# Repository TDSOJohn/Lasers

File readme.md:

# Monochrome Laser Bar

This repo contains the schematics and software for the monochrome laser bars used by VirtualConcrete.

Hardware:
- Aluminum body
- Up to 6 laser diodes
- Custom designed pcb with [Arduino Nano](https://docs.arduino.cc/hardware/nano/) and up to 6 laser drivers
- Custom variation of ethernet poe to supply everything with a single RJ45
- DMX over RJ45 control mode
- Fun mode

Software:
- Reads DMX input using [DMXSerial](https://github.com/mathertel/DMXSerial)
- Writes dimmer values as PWM

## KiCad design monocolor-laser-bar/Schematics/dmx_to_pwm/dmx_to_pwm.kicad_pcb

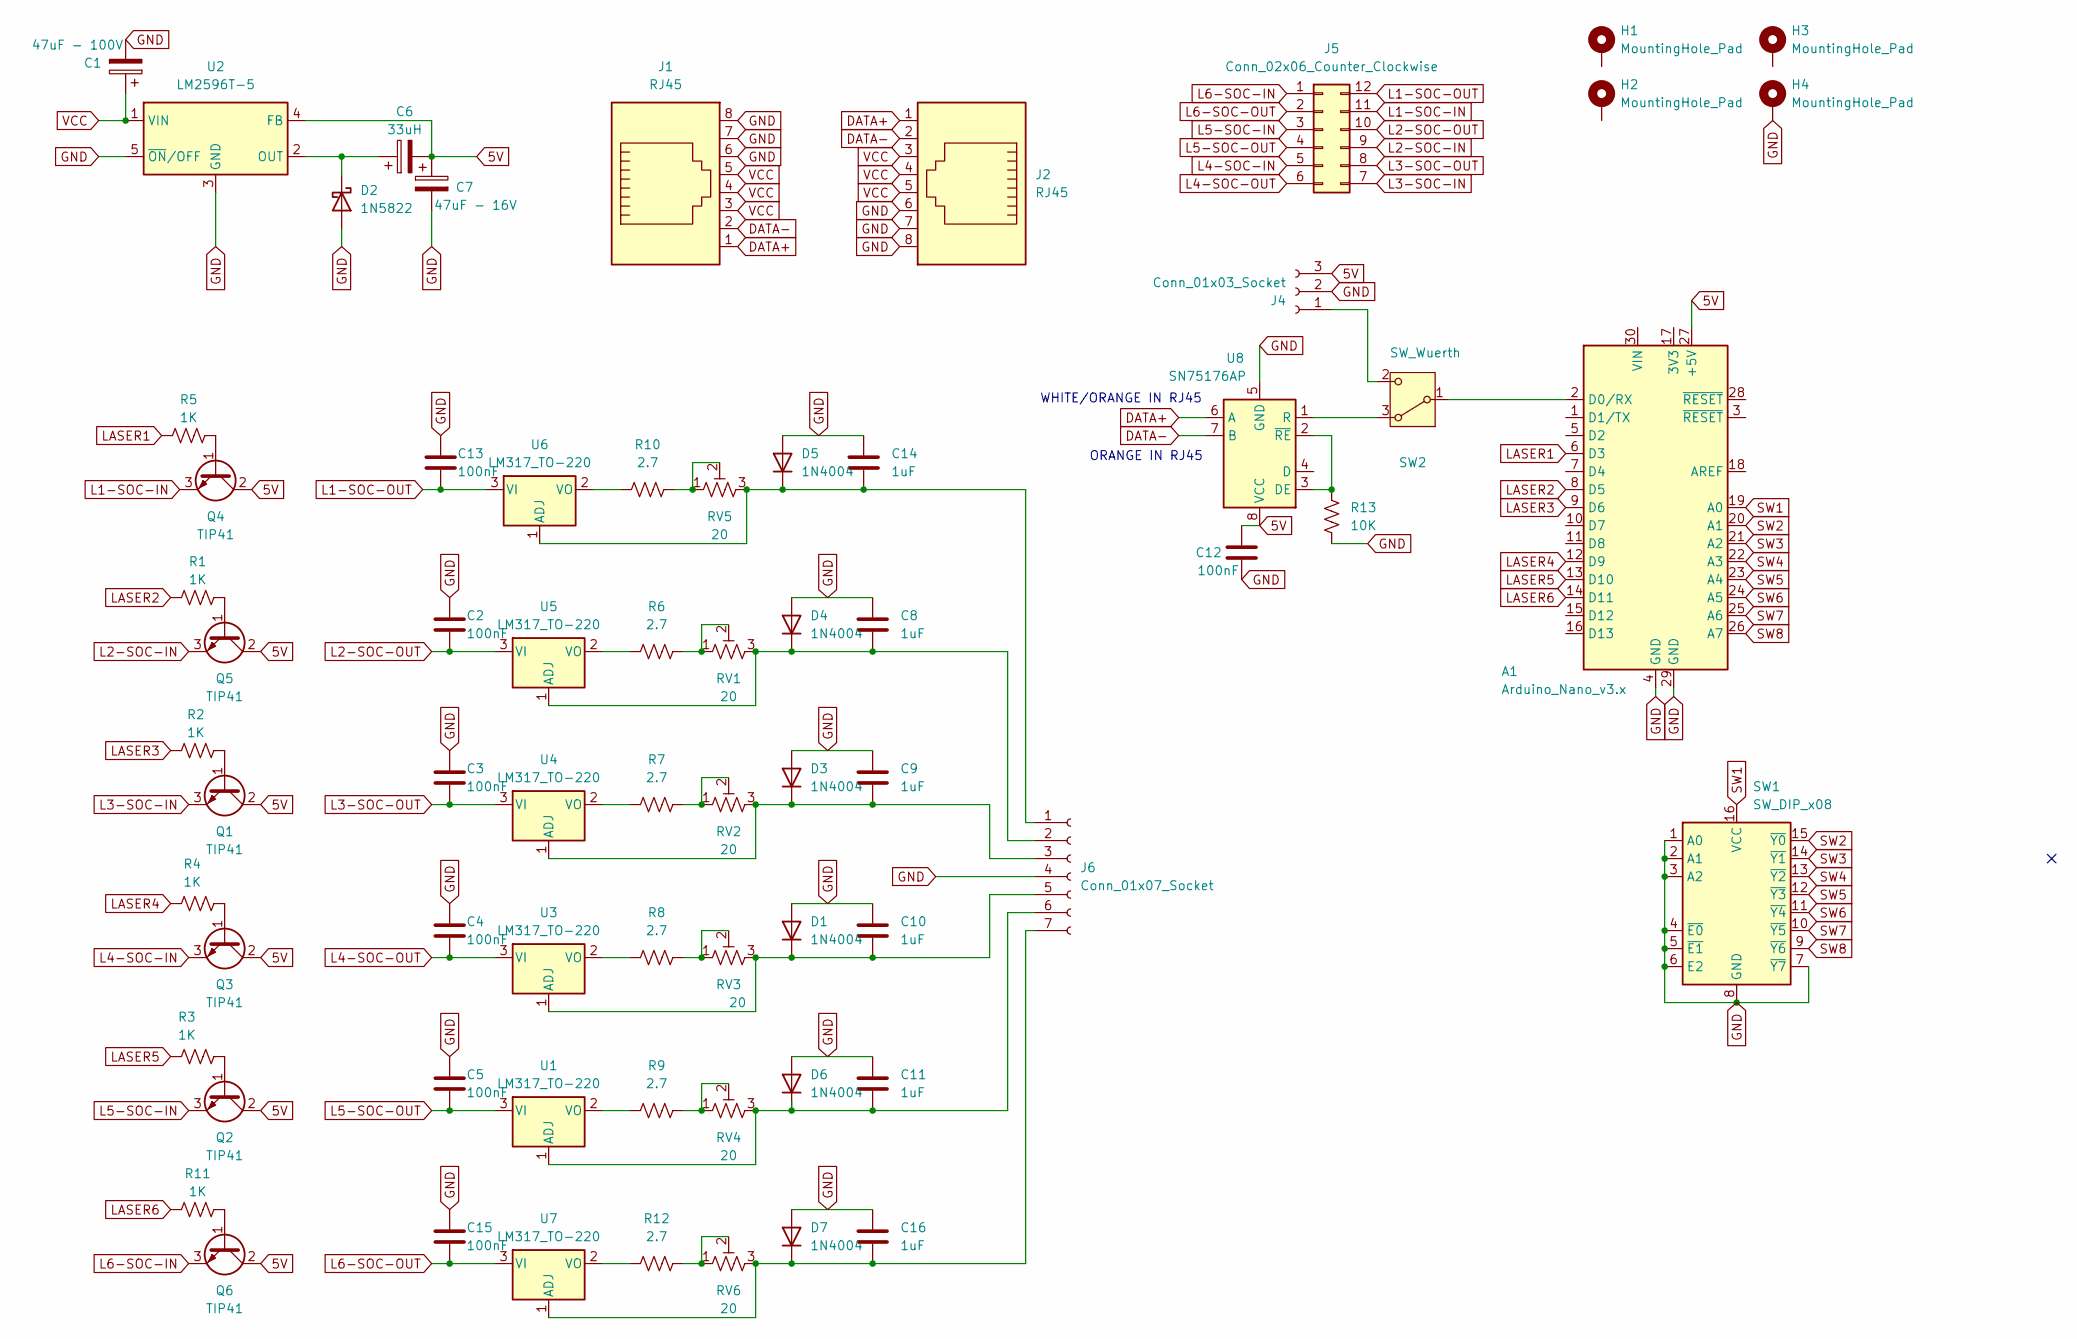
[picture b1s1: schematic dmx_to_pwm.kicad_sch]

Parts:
A1: Arduino_Nano_v3.x; Arduino_Nano
C1: 47uF - 100V; CP_Radial_D7.5mm_P2.50mm
C2, C3, C4, C5, C12, C13, C15: 100nF; C_Disc_D3.0mm_W2.0mm_P2.50mm
C6: 33uH; CP_Radial_D8.0mm_P5.00mm
C7: 47uF - 16V; CP_Radial_D7.5mm_P2.50mm
C8, C9, C10, C11, C14, C16: 1uF; C_Disc_D3.0mm_W2.0mm_P2.50mm
D1, D3, D4, D5, D6, D7: 1N4004; D_DO-41_SOD81_P7.62mm_Horizontal
D2: 1N5822; D_DO-201AD_P15.24mm_Horizontal
H1, H2, H3, H4: MountingHole_Pad; MountingHole_3.2mm_M3_Pad
J1, J2: RJ45; RJ45_Amphenol_54602-x08_Horizontal
J4: Conn_01x03_Socket; JST_EH_B3B-EH-A_1x03_P2.50mm_Vertical
J5: Conn_02x06_Counter_Clockwise; PinHeader_2x06_P2.54mm_Vertical
J6: Conn_01x07_Socket; JST_EH_B7B-EH-A_1x07_P2.50mm_Vertical
Q1, Q2, Q3, Q4, Q5, Q6: TIP41; TO-220-3_Vertical
R1, R2, R3, R4, R5, R11: 1K; R_Axial_DIN0207_L6.3mm_D2.5mm_P7.62mm_Horizontal
R6, R7, R8, R9, R10, R12: 2.7; R_Axial_DIN0411_L9.9mm_D3.6mm_P12.70mm_Horizontal
R13: 10K; R_Axial_DIN0414_L11.9mm_D4.5mm_P7.62mm_Vertical
RV1, RV2, RV3, RV4, RV5, RV6: 20; Potentiometer_Bourns_3296Z_Horizontal
SW1: SW_DIP_x08; DIP-16_W7.62mm_LongPads
SW2: SW_Wuerth; SW_Slide-03_Wuerth-WS-SLTV_10x2.5x6.4_P2.54mm
U1, U3, U4, U5, U6, U7: LM317_TO-220; TO-220-3_Vertical
U2: LM2596T-5; TO-220-5_P3.4x3.7mm_StaggerOdd_Lead3.8mm_Vertical
U8: SN75176AP; DIP-8_W7.62mm_Socket_LongPads

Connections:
5V: A1.27 (+5V), C6.2, C7.1, C12.1, J4.3, Q1.2 (C), Q2.2 (C), Q3.2 (C), Q4.2 (C), Q5.2 (C), Q6.2 (C), U2.4 (FB), U8.8 (VCC)
DATA+: J1.1, J2.1, U8.6 (A)
DATA-: J1.2, J2.2, U8.7 (B)
GND: A1.4 (GND), A1.29 (GND), C1.2, C2.1, C3.1, C4.1, C5.1, C7.2, C8.1, C9.1, C10.1, C11.1, C12.2, C13.1, C14.1, C15.1, C16.1, D1.2 (A), D2.2 (A), D3.2 (A), D4.2 (A), D5.2 (A), D6.2 (A), D7.2 (A), H4.1, J1.6, J1.7, J1.8, J2.6, J2.7, J2.8, J4.2, J6.4, R13.1, SW1.1 (A0), SW1.2 (A1), SW1.3 (A2), SW1.4 (~E0), SW1.5 (~E1), SW1.6 (E2), SW1.7 (~Y7), SW1.8 (GND), U2.3 (GND), U2.5 (~ON/OFF), U8.5 (GND)
L1-SOC-IN: J5.11, Q4.3 (E)
L1-SOC-OUT: C13.2, J5.12, U6.3 (VI)
L2-SOC-IN: J5.9, Q5.3 (E)
L2-SOC-OUT: C2.2, J5.10, U5.3 (VI)
L3-SOC-IN: J5.7, Q1.3 (E)
L3-SOC-OUT: C3.2, J5.8, U4.3 (VI)
L4-SOC-IN: J5.5, Q3.3 (E)
L4-SOC-OUT: C4.2, J5.6, U3.3 (VI)
L5-SOC-IN: J5.3, Q2.3 (E)
L5-SOC-OUT: C5.2, J5.4, U1.3 (VI)
L6-SOC-IN: J5.1, Q6.3 (E)
L6-SOC-OUT: C15.2, J5.2, U7.3 (VI)
LASER1: A1.6 (D3), R5.2
LASER2: A1.8 (D5), R1.2
LASER3: A1.9 (D6), R2.2
LASER4: A1.12 (D9), R4.2
LASER5: A1.13 (D10), R3.2
LASER6: A1.14 (D11), R11.2
unnamed: A1.2 (D0/RX), SW2.1 (B)
unnamed: C10.2, D1.1 (K), J6.5, RV3.3, U3.1 (ADJ)
unnamed: C6.1, D2.1 (K), U2.2 (OUT)
unnamed: C9.2, D3.1 (K), J6.3, RV2.3, U4.1 (ADJ)
unnamed: C8.2, D4.1 (K), J6.2, RV1.3, U5.1 (ADJ)
unnamed: C14.2, D5.1 (K), J6.1, RV5.3, U6.1 (ADJ)
unnamed: C11.2, D6.1 (K), J6.6, RV4.3, U1.1 (ADJ)
unnamed: C16.2, D7.1 (K), J6.7, RV6.3, U7.1 (ADJ)
unnamed: J4.1, SW2.2 (C)
unnamed: Q1.1 (B), R2.1
unnamed: Q2.1 (B), R3.1
unnamed: Q3.1 (B), R4.1
unnamed: Q4.1 (B), R5.1
unnamed: Q5.1 (B), R1.1
unnamed: Q6.1 (B), R11.1
unnamed: R6.1, RV1.1, RV1.2
unnamed: R7.1, RV2.1, RV2.2
unnamed: R8.1, RV3.1, RV3.2
unnamed: R9.1, RV4.1, RV4.2
unnamed: R10.1, RV5.1, RV5.2
unnamed: R12.1, RV6.1, RV6.2
unnamed: SW2.3 (A), U8.1 (R)
unnamed: R9.2, U1.2 (VO)
unnamed: R8.2, U3.2 (VO)
unnamed: R7.2, U4.2 (VO)
unnamed: R6.2, U5.2 (VO)
unnamed: R10.2, U6.2 (VO)
unnamed: R12.2, U7.2 (VO)
unnamed: R13.2, U8.2 (~RE), U8.3 (DE)
SW1: A1.19 (A0), SW1.16 (VCC)
SW2: A1.20 (A1), SW1.15 (~Y0)
SW3: A1.21 (A2), SW1.14 (~Y1)
SW4: A1.22 (A3), SW1.13 (~Y2)
SW5: A1.23 (A4), SW1.12 (~Y3)
SW6: A1.24 (A5), SW1.11 (~Y4)
SW7: A1.25 (A6), SW1.10 (~Y5)
SW8: A1.26 (A7), SW1.9 (~Y6)
VCC: C1.1, J1.3, J1.4, J1.5, J2.3, J2.4, J2.5, U2.1 (VIN)

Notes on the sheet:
WHITE/ORANGE IN RJ45
ORANGE IN RJ45

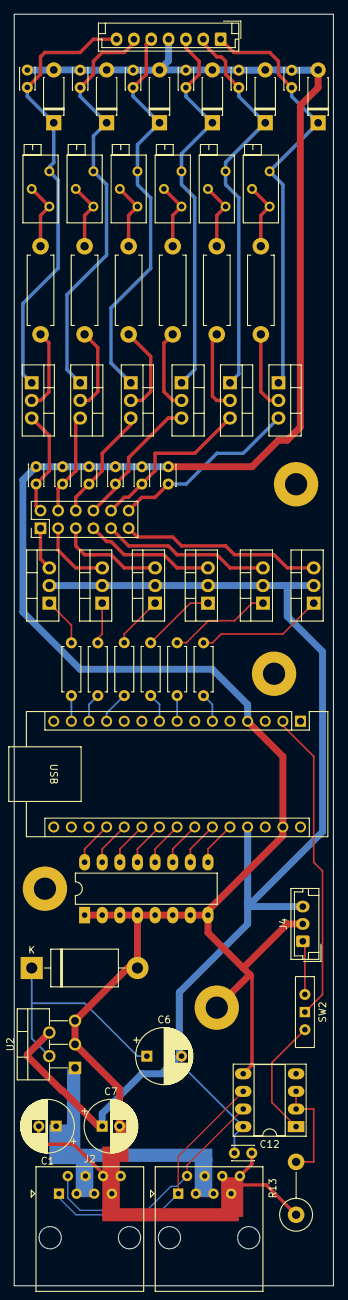
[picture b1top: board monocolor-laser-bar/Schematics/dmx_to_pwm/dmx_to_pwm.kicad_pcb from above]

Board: 2 copper layers, 46.0 x 183.2 mm, 68 parts (0 on the bottom side), 60 nets.

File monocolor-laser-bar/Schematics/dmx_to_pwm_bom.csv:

"Id";"Designator";"Footprint";"Quantity";"Designation";"Supplier and ref";
1;"C10,C14,C9,C16,C8,C11";"C_Disc_D3.0mm_W2.0mm_P2.50mm";6;"1uF";;;
2;"C5,C4,C2,C12,C13,C3,C15";"C_Disc_D3.0mm_W2.0mm_P2.50mm";7;"100nF";;;
3;"D7,D6,D1,D5,D3,D4";"D_DO-41_SOD81_P7.62mm_Horizontal";6;"1N4004";;;
4;"C6";"CP_Radial_D8.0mm_P5.00mm";1;"33uH";;;
5;"U7,U3,U4,U5,U1,U6";"TO-220-3_Vertical";6;"LM317_TO-220";;;
6;"RV2,RV3,RV4,RV6,RV1,RV5";"Potentiometer_Bourns_3296Z_Horizontal";6;"20";;;
7;"C7";"CP_Radial_D7.5mm_P2.50mm";1;"47uF - 16V";;;
8;"D2";"D_DO-201AD_P15.24mm_Horizontal";1;"1N5822";;;
9;"R5,R4,R2,R3,R1,R11";"R_Axial_DIN0207_L6.3mm_D2.5mm_P7.62mm_Horizontal";6;"1K";;;
10;"R9,R6,R8,R7,R12,R10";"R_Axial_DIN0411_L9.9mm_D3.6mm_P12.70mm_Horizontal";6;"2.7";;;
11;"Q6,Q5,Q2,Q3,Q1,Q4";"TO-220-3_Vertical";6;"TIP41";;;
12;"J5";"PinHeader_2x06_P2.54mm_Vertical";1;"Conn_02x06_Counter_Clockwise";;;
13;"R13";"R_Axial_DIN0414_L11.9mm_D4.5mm_P7.62mm_Vertical";1;"10K";;;
14;"J1,J2";"RJ45_Amphenol_54602-x08_Horizontal";2;"RJ45";;;
15;"SW1";"DIP-16_W7.62mm_LongPads";1;"SW_DIP_x08";;;
16;"J4";"JST_EH_B3B-EH-A_1x03_P2.50mm_Vertical";1;"Conn_01x03_Socket";;;
17;"U2";"TO-220-5_P3.4x3.7mm_StaggerOdd_Lead3.8mm_Vertical";1;"LM2596T-5";;;
18;"U8";"DIP-8_W7.62mm_Socket_LongPads";1;"SN75176AP";;;
19;"C1";"CP_Radial_D7.5mm_P2.50mm";1;"47uF - 100V";;;
20;"SW2";"SW_Slide-03_Wuerth-WS-SLTV_10x2.5x6.4_P2.54mm";1;"SW_Wuerth";;;
21;"J6";"JST_EH_B7B-EH-A_1x07_P2.50mm_Vertical";1;"Conn_01x07_Socket";;;
22;"A1";"Arduino_Nano";1;"Arduino_Nano_v3.x";;;

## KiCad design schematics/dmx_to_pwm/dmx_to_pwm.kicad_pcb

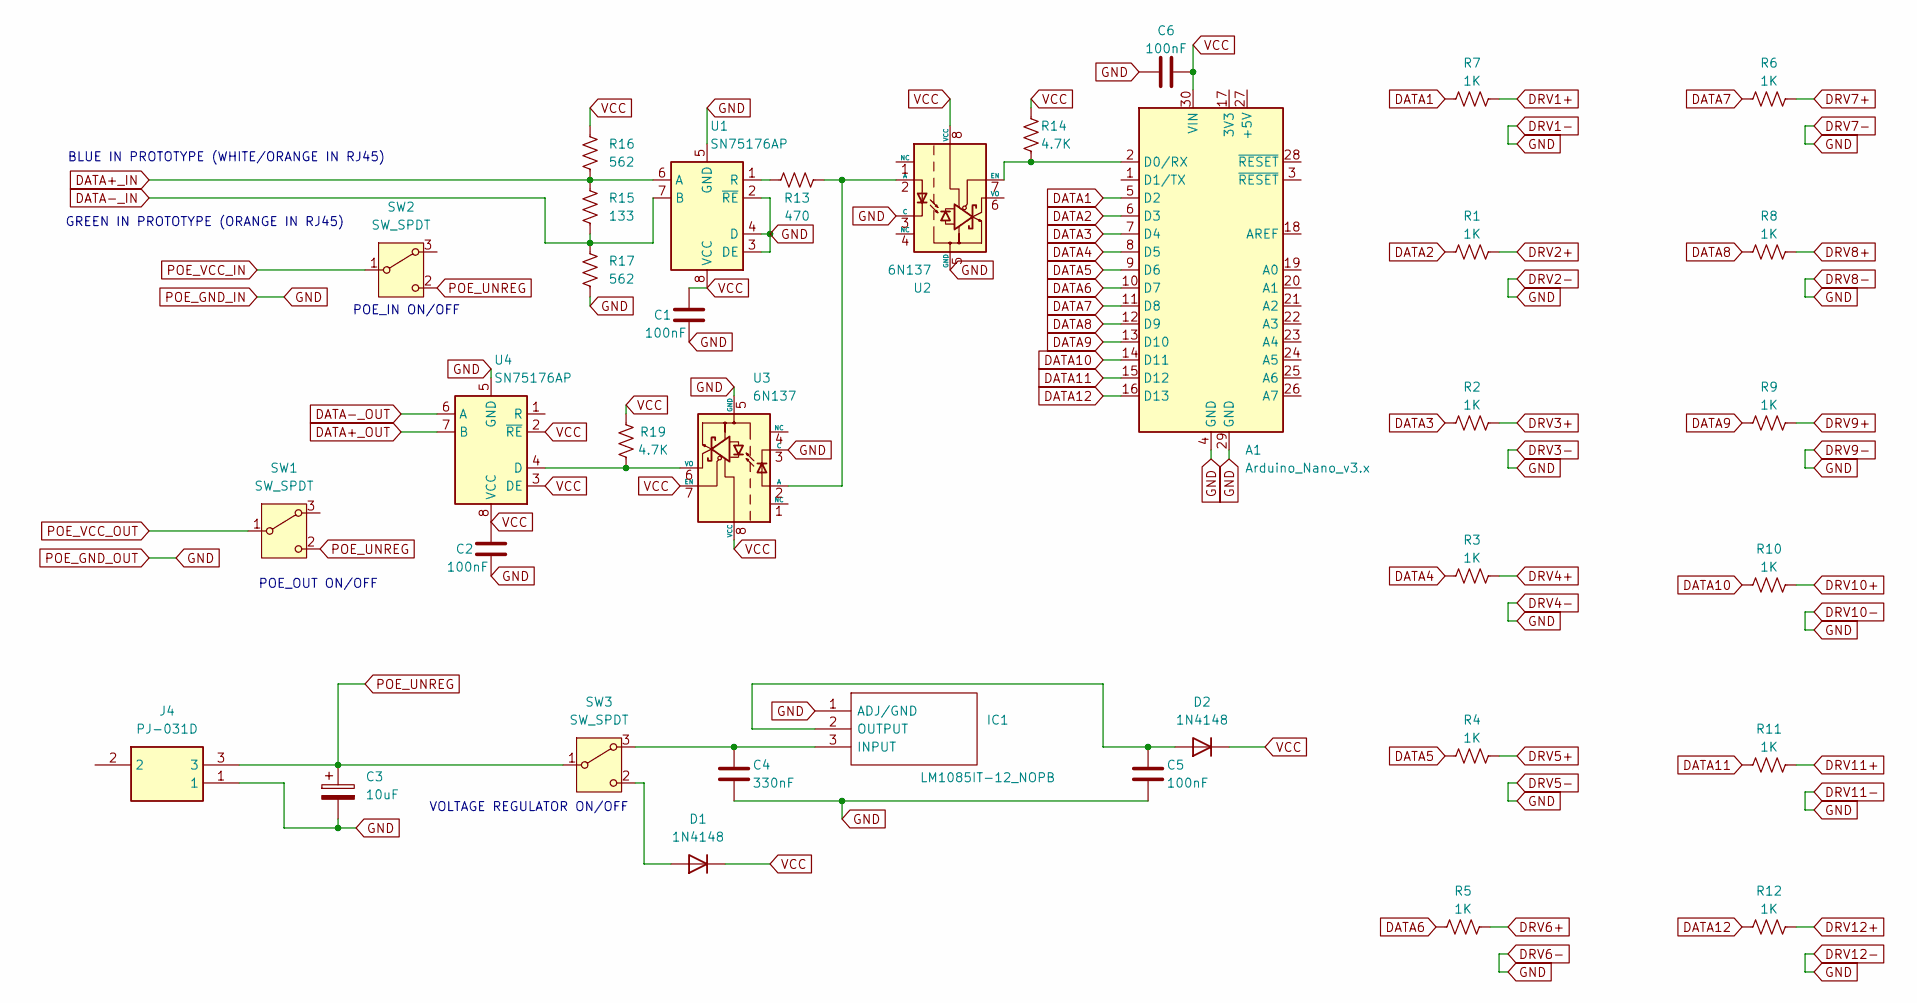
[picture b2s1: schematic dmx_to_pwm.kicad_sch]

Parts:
A1: Arduino_Nano_v3.x; Arduino_Nano
C1, C2, C5: 100nF; C_Disc_D3.0mm_W2.0mm_P2.50mm
C3: 10uF; CP_Radial_Tantal_D5.5mm_P2.50mm
C4: 330nF; CP_Radial_Tantal_D5.5mm_P2.50mm
C6: 100nF
D1, D2: 1N4148; D_DO-35_SOD27_P7.62mm_Horizontal
IC1: LM1085IT-12_NOPB; TO254P470X1028X1955-3P; Manufacturer_Part_Number LM1085IT-12/NOPB; Mouser Part Number 926-LM1085IT-12/NOPB
J4: PJ-031D; PJ031D; Manufacturer_Part_Number PJ-031D; Mouser Part Number 490-PJ-031D
R1, R2, R3, R4, R5, R6, R7, R8, R9, R10, R11, R12: 1K; R_Axial_DIN0204_L3.6mm_D1.6mm_P7.62mm_Horizontal
R13: 470; R_Axial_DIN0204_L3.6mm_D1.6mm_P7.62mm_Horizontal
R14, R19: 4.7K; R_Axial_DIN0204_L3.6mm_D1.6mm_P7.62mm_Horizontal
R15: 133; R_Axial_DIN0204_L3.6mm_D1.6mm_P7.62mm_Horizontal
R16, R17: 562; R_Axial_DIN0204_L3.6mm_D1.6mm_P7.62mm_Horizontal
SW1, SW2, SW3: SW_SPDT; SW_Slide-03_Wuerth-WS-SLTV_10x2.5x6.4_P2.54mm
U1, U4: SN75176AP; DIP-8_W7.62mm
U2, U3: 6N137; DIP-8_W7.62mm

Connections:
DATA1: A1.5 (D2), R7.1
DATA2: A1.6 (D3), R1.1
DATA3: A1.7 (D4), R2.1
DATA4: A1.8 (D5), R3.1
DATA5: A1.9 (D6), R4.1
DATA6: A1.10 (D7), R5.1
DATA7: A1.11 (D8), R6.1
DATA8: A1.12 (D9), R8.1
DATA9: A1.13 (D10), R9.1
DATA10: A1.14 (D11), R10.1
DATA11: A1.15 (D12), R11.1
DATA12: A1.16 (D13), R12.1
DATA+_IN: R15.1, R16.2, U1.6 (A)
DATA+_OUT: U4.7 (B)
DATA-_IN: R15.2, R17.1, U1.7 (B)
DATA-_OUT: U4.6 (A)
DRV1+: R7.2
DRV1-: A1.4 (GND), A1.29 (GND), C1.2, C2.2, C3.2, C4.2, C5.2, C6.1, IC1.1 (ADJ/GND), J4.1, R17.2, U1.2 (~RE), U1.3 (DE), U1.4 (D), U1.5 (GND), U2.3 (C), U2.5 (GND), U3.3 (C), U3.5 (GND), U4.5 (GND)
DRV2+: R1.2
DRV3+: R2.2
DRV4+: R3.2
DRV5+: R4.2
DRV6+: R5.2
DRV7+: R6.2
DRV8+: R8.2
DRV9+: R9.2
DRV10+: R10.2
DRV11+: R11.2
DRV12+: R12.2
unnamed: A1.2 (D0/RX), R14.2, U2.7 (EN)
unnamed 30: D1.2 (A), SW3.2 (C); also elsewhere on the board
unnamed: C5.1, D2.2 (A), IC1.2 (OUTPUT)
unnamed 33: SW1.1 (B); also elsewhere on the board
unnamed: R13.1, U1.1 (R)
unnamed: R13.2, U2.2 (A), U3.2 (A)
unnamed: R19.1, U3.6 (VO), U4.4 (D)
TO_POE_UNREG: C3.1, J4.3, SW1.2 (C), SW2.2 (C), SW3.1 (B)
UNREGULATED_IN: C4.1, IC1.3 (INPUT), SW3.3 (A)

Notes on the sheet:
VOLTAGE REGULATOR ON/OFF
POE_OUT ON/OFF
POE_IN ON/OFF
GREEN IN PROTOTYPE (ORANGE IN RJ45)
BLUE IN PROTOTYPE (WHITE/ORANGE IN RJ45)

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
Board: 2 copper layers, 36 parts (0 on the bottom side), 26 nets, no tracks yet.

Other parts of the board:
SW1#2: SW_SPST; SW_Slide-03_Wuerth-WS-SLTV_10x2.5x6.4_P2.54mm

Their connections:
unnamed 30: SW1#2.2 (C); also elsewhere on the board
unnamed 33: SW1#2.1 (B); also elsewhere on the board

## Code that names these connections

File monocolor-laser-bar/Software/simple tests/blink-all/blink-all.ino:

const int Laser1 = 3;
const int Laser2 = 5;
const int Laser3 = 6;
const int Laser4 = 9;
const int Laser5 = 10;
const int Laser6 = 11;


void setup() {
  pinMode(Laser1, OUTPUT);
  pinMode(Laser2, OUTPUT);
  pinMode(Laser3, OUTPUT);
  pinMode(Laser4, OUTPUT);
  pinMode(Laser5, OUTPUT);
  pinMode(Laser6, OUTPUT);

  analogWrite(Laser1, 255);
  analogWrite(Laser2, 255);
  analogWrite(Laser3, 255);
  analogWrite(Laser4, 255);
  analogWrite(Laser5, 255);
  analogWrite(Laser6, 255);
}

int step = 0;

void loop() {
  analogWrite(Laser1, 255);
  analogWrite(Laser2, 255);
  analogWrite(Laser3, 255);
  analogWrite(Laser4, 255);
  analogWrite(Laser5, 255);
  analogWrite(Laser6, 255);

  delay(5000);

  analogWrite(Laser1, 0);
  analogWrite(Laser2, 0);
  analogWrite(Laser3, 0);
  analogWrite(Laser4, 0);
  analogWrite(Laser5, 0);
  analogWrite(Laser6, 0);

  delay(5000);
}

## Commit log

2023-01-10 Added mainboard schematics
2024-02-03 added alluminum bar cad
2024-02-04 added antenna footprint
2024-02-05 added laser drivers
2024-02-13 added laser blocks, improved laser bar
2024-02-17 added project for 2 colliders
2024-02-22 dmx to pwm first commit
2024-02-26 updated dmx-to-pwm schematics
2024-02-29 added software to dimmer rgb
2024-02-29 added some exports
2024-02-29 updated bar size
2024-02-29 added blocco laser export
2024-02-29 added blocco laser stp export
2024-02-29 updated to kicad version 8.0
2024-03-01 updated some components
2024-03-05 improved schematics
2024-03-08 #7 added rgb diode volume
2024-03-08 #5 improved schematics
2024-03-11 added some prototype info to the schematics
2024-03-11 #2 Aggiunto_prosetto_barre_moduli
2024-03-23 updated schematics, added laser module blender file
2024-03-23 deleted pdf
2024-03-29 render is now properly working with qlc+
2024-05-14 improved control code
2024-05-14 added some notes
2024-06-19 cleaned up files and folders
2024-06-19 improved folder structure, deleted useless file
2024-06-19 added todo
2024-06-20 first code for mono colored bars
2024-06-23 changed last packet timeout to better debug
2024-06-24 debugging software
2024-06-25 debugging
2024-06-26 updated todos
2024-06-26 removed debugging file
2024-06-26 improved code
2024-06-26 added pdf schematics
2024-06-26 updated todo
2024-07-03 updated fun mode
2024-07-07 added smoke machine schematics
2024-07-09 added fun mode to dmx code
2024-07-14 added interrupt code
2024-07-15 created max patch
2024-07-22 improved qlc file
2024-08-21 Added drivers to monochrome schematics
2024-08-22 Documenti_Sviluppo_Brand
2024-09-03 improved qlc patches
2024-09-04 updated schematics
2024-09-04 improved max patches
2024-09-04 improved folders
2024-09-04 updated rj45
2024-09-04 first pcb layout
2024-09-09 added board
2024-09-09 added export
2024-09-09 added gerber output
2024-09-09 uploaded artifacts
2024-09-09 updated artifacts
2024-09-09 updated max patches
2024-09-13 added 6 laser control code
2024-09-14 300 scalini control project
2024-09-15 updated arduino code
2024-09-22 updated software
2024-09-28 added debug software
2024-10-20 improved pcb track width, added antenna connector
2024-10-20 added dip switch code
2024-11-12 stuff
2024-11-21 updated schematics to 6 lasers
2024-11-21 updated pcb for 6 lasers
2024-11-24 improved pcb
2024-12-03 improved arduino code
2024-12-28 cleaned repo
2025-01-07 updated CADs
2025-01-21 fixed some arduino code
2025-02-24 fixes
2025-03-08 Update dmx-in-generic.ino
    improved code
2025-03-26 deleted useless code
2025-03-26 added readme
2025-05-28 updated schematics and software
2025-06-17 deleted useless rgb stuff
2025-09-07 updated to v9
2025-10-21 analog write on wrong pin gave funny output
2026-02-12 Only laser stuff remaining
2026-02-18 deleted some useless stuff
